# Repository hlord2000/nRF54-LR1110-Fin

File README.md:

# LR1110 Expansion Board for nRF54L15-DK

This expansion board connects the Semtech LR1110 RF transceiver to the Nordic nRF54L15-DK. The board enables LoRa, GNSS, and Wi-Fi scanning capabilities.

## Features

- Supports LoRa connectivity via 0900PC16J0042001E filter and SKY13380-350LF RF switch
- GNSS and Wi-Fi scanning via 2000PC15C0040001E filter (IPDs enable smaller solution size)
- Onboard LNA for non-active GNSS antennas
- 32 MHz TCXO with power-saving VTCXO control from LR1110
- 32.768 KHz crystal for timing reference
- Level shifters to support all possible IO voltages of the nRF54L15
- Compatible with the new nRF54L15 headers

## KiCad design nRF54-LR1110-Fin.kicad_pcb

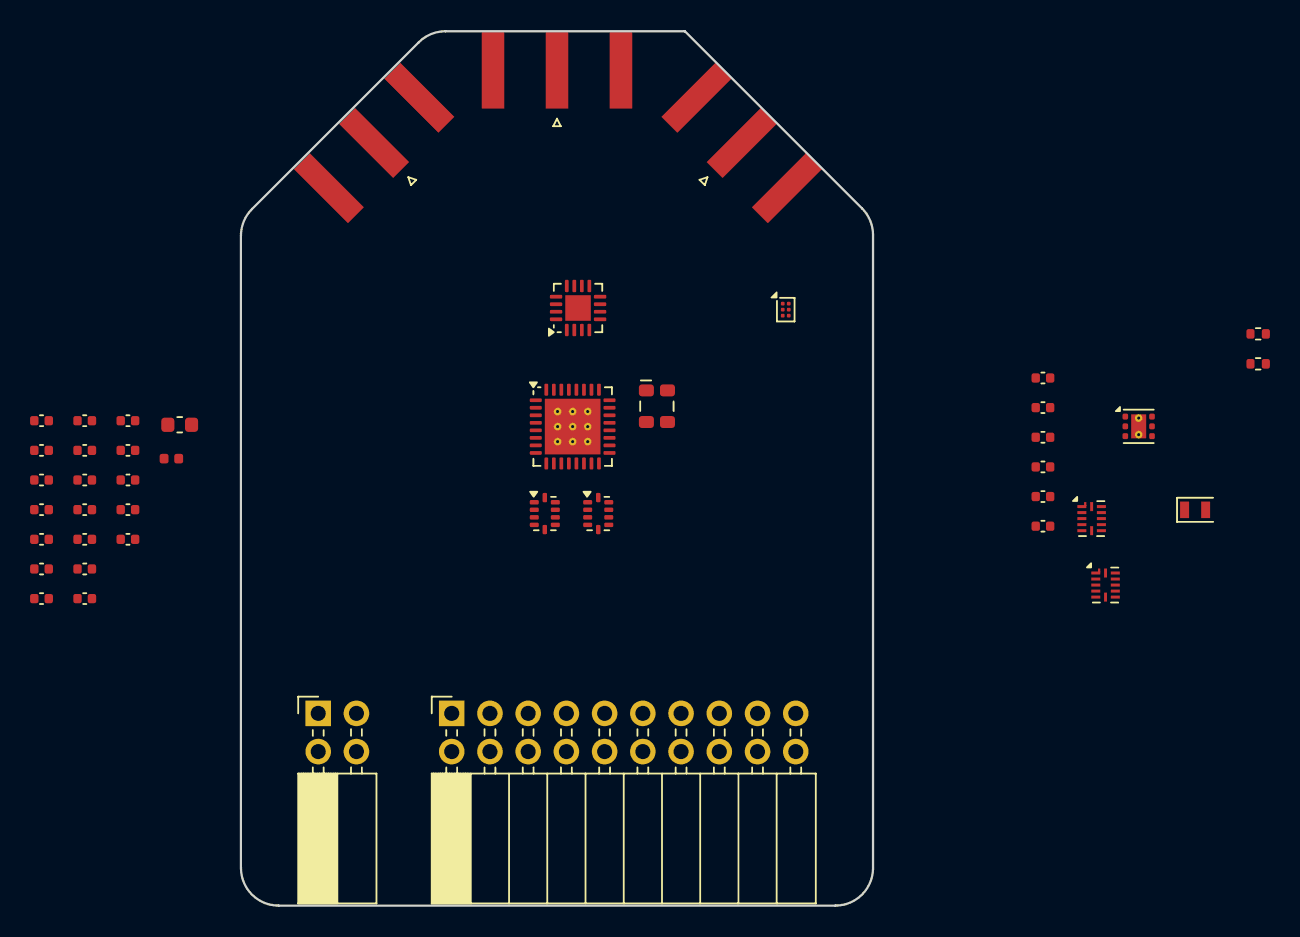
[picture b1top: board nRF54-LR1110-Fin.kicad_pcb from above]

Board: 2 copper layers, 42.0 x 58.1 mm, 44 parts (0 on the bottom side), 46 nets, no tracks yet.

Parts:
AE1, AE2, AE3: Antenna_Shield; SMA_Amphenol_132289_EdgeMount
C1: 470nF; C_0402_1005Metric
C2, C3, C5, C8, C10, C11, C12, C15, C16: 100nF; C_0402_1005Metric
C4: 47pF; C_0402_1005Metric
C6, C7: 12pF; C_0402_1005Metric
C9: 1nF; C_0402_1005Metric
C13, C14: 1uF; C_0402_1005Metric
FL1: 0900PC16J0042001E; Balun_Johanson_0900FM15K0039
FL2: 2000PC15C0040001E; Balun_Johanson_0900FM15K0039
GPIO1: Conn_02x10_Odd_Even; PinSocket_2x10_P2.54mm_Horizontal
L1: 15uH; L_0603_1608Metric
L2: 12nH; L_0402_1005Metric
R1, R2: 100kR; R_0402_1005Metric
U1: LR1110IMLTRT; QFN-32-1EP_5x5mm_P0.5mm_EP3.7x3.7mm_ThermalVias
U2: SKY13380-350LF; QFN-16-1EP_3x3mm_P0.5mm_EP1.7x1.7mm
U3: BGA535N6; Infineon_PG-TSNP-6-10_0.7x1.1mm_0.7x1.1mm_P0.4mm
U4, U6: TXB0104RUT; Texas_R-PUQFN-N12
U5: TLV75533PDRV; WSON-6-1EP_2x2mm_P0.65mm_EP1x1.6mm_ThermalVias
VSUP1: Conn_02x02_Odd_Even; PinSocket_2x02_P2.54mm_Horizontal
Y1: TG2520SMN 32.0000M-MCGNNM3; Oscillator_SMD_SeikoEpson_TG2520SMN-xxx-xxxxxx-4Pin_2.5x2.0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
Y2: 32.768KHz; Crystal_SMD_2012-2Pin_2.0x1.2mm
Z1, Z2, Z3, Z4, Z5, Z6, Z7, Z8, Z9: R_Small; C_0402_1005Metric

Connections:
/BUSY: U1.25 (BUSY), U4.2 (A1)
/CIPO: U1.21 (CIPO), U6.2 (A1)
/COPI: U1.22 (COPI), U4.5 (A4)
/GNSSLP1: U1.11 (DIO7), U3.4 (C2)
/GNSSLP2: U1.10 (DIO8), U3.6 (C1)
/IRQ: U1.9 (IRQ), U6.3 (A2)
/P1.04: GPIO1.7, U4.8 (B3)
/P1.05: GPIO1.8, U4.7 (B4)
/P1.06: GPIO1.9, U6.10 (B1)
/P1.07: GPIO1.10, U4.9 (B2)
/P1.08: GPIO1.11, U4.10 (B1)
/P1.09: GPIO1.12, U6.9 (B2)
/P1.10: GPIO1.13, U6.8 (B3)
/PCK: U1.23 (PCK), U4.4 (A3)
/RFSW1: U1.20 (DIO5), U2.4 (CTRL1)
/RFSW2: U1.19 (DIO6), U2.3 (CTRL2)
/~CS: U1.24 (~CS), U4.3 (A2)
/~RESET: U1.6 (~RESET), U6.4 (A3)
GND: AE1.2 (Shield), AE2.2 (Shield), AE3.2 (Shield), C1.2, C2.2, C3.2, C4.2, C5.1, C6.1, C7.2, C8.2, C10.2, C11.1, C12.1, C13.1, C14.1, C15.1, C16.1, FL1.5 (GND), FL1.7 (GND), FL1.10 (GND), FL2.3 (GND), FL2.5 (GND), FL2.6 (GND), FL2.9 (GND), FL2.10 (GND), GPIO1.2, GPIO1.19, R1.2, R2.2, U1.13 (GND), U1.33 (EP), U2.1 (GND), U2.5 (GND), U2.7 (GND), U2.9 (GND), U2.10 (GND), U2.12 (GND), U2.14 (GND), U3.1 (G), U4.6 (GND), U5.3 (GND), U5.7 (GND), U6.5 (A4), U6.6 (GND), U6.7 (B4), VSUP1.2, VSUP1.4, Y1.2 (GND), Z2.1, Z3.1, Z4.1, Z6.1, Z7.1, Z9.1
unnamed: AE1.1 (A), Z1.2, Z3.2
unnamed: AE2.1 (A), Z5.2, Z6.2
unnamed: AE3.1 (A), Z8.2, Z9.2
unnamed: C9.1, L2.2
unnamed: C9.2, Z4.2, Z5.1
unnamed: FL1.4 (RFI_N_LFO), U1.29 (RFI_N_LF0)
unnamed: FL1.3 (RFI_P_LFO), U1.30 (RFI_P_LF0)
unnamed: FL1.1 (RFO_HP_LF), U1.32 (RFO_HP_LF)
unnamed: FL1.2 (RFO_LP_LF), U1.31 (RFO_LP_LF)
unnamed: FL1.6 (RX), U2.8 (RF3)
unnamed: FL1.9 (TX_HP), U2.13 (RF1)
unnamed: FL1.8 (TX_LP), U2.15 (RF2)
unnamed: FL2.8 (GNSS), U3.3
unnamed: FL2.4 (RFIO_HF), U1.26 (RFIO_HF)
unnamed: FL2.2 (RFI_N_LF1), U1.27 (RFI_N_LF1)
unnamed: FL2.1 (RFI_P_LF1), U1.28 (RFI_P_LF1)
unnamed: FL2.7 (WIFI), Z7.2, Z8.1
unnamed: L2.1, U3.5
unnamed: C7.1, U1.8 (32K_N), Y2.1
unnamed: C6.2, U1.7 (32K_P), Y2.2
unnamed: C1.1, L1.2, U1.14 (DCC_SW)
unnamed: L1.1, U1.12 (VREG)
unnamed: U1.4 (TCXO_IN), Y1.3 (OUT)
unnamed: U2.11 (ANT), Z1.1, Z2.2
VBUS: C13.2, U5.4 (EN), U5.6 (IN), VSUP1.1
VDD: C2.1, C3.1, C4.1, C5.2, C8.1, C10.1, C11.2, C14.2, C15.2, R1.1, R2.1, U1.2 (VBAT_RF), U1.3 (VTCXO), U1.15 (VBAT), U2.2 (VDD), U3.2 (V), U4.1 (VCCA), U4.12 (OE), U5.1 (OUT), U6.1 (VCCA), U6.12 (OE), Y1.4 (Vcc)
VDDIO: C12.2, C16.2, GPIO1.1, GPIO1.20, U4.11 (VCCB), U6.11 (VCCB)

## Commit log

2025-03-18 Initial commit.
2025-04-18 schematic: add level shifter, gnss amp
    Adds level shifter to L15-DK, GNSS amplifier, proper handling of RF
    components for LoRA radio, initial board outline.
2025-04-18 license: add CERN-OHL-P-V2
    adds CERN-OHL-P-V2 license to repo
